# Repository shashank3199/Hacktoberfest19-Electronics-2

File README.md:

# Electronics-2

## Introduction
This repository contains the board design for Manual Bot Controller Shield for Arduino Mega 2560.

## Layout

### Board File -

### Schematic File -

## Files in the Repository
The files in the repository are :

#### ManualBot_Shield.brd
This is the Board file and contains the Blueprint of the Shield Layout (Prototype).

#### ManualBot_Shield.sch
This is the Schematic file and contains the actual circuitary behind the Shield.

#### README.md
The Description file containing details about the repository. The file that you looking at right now.

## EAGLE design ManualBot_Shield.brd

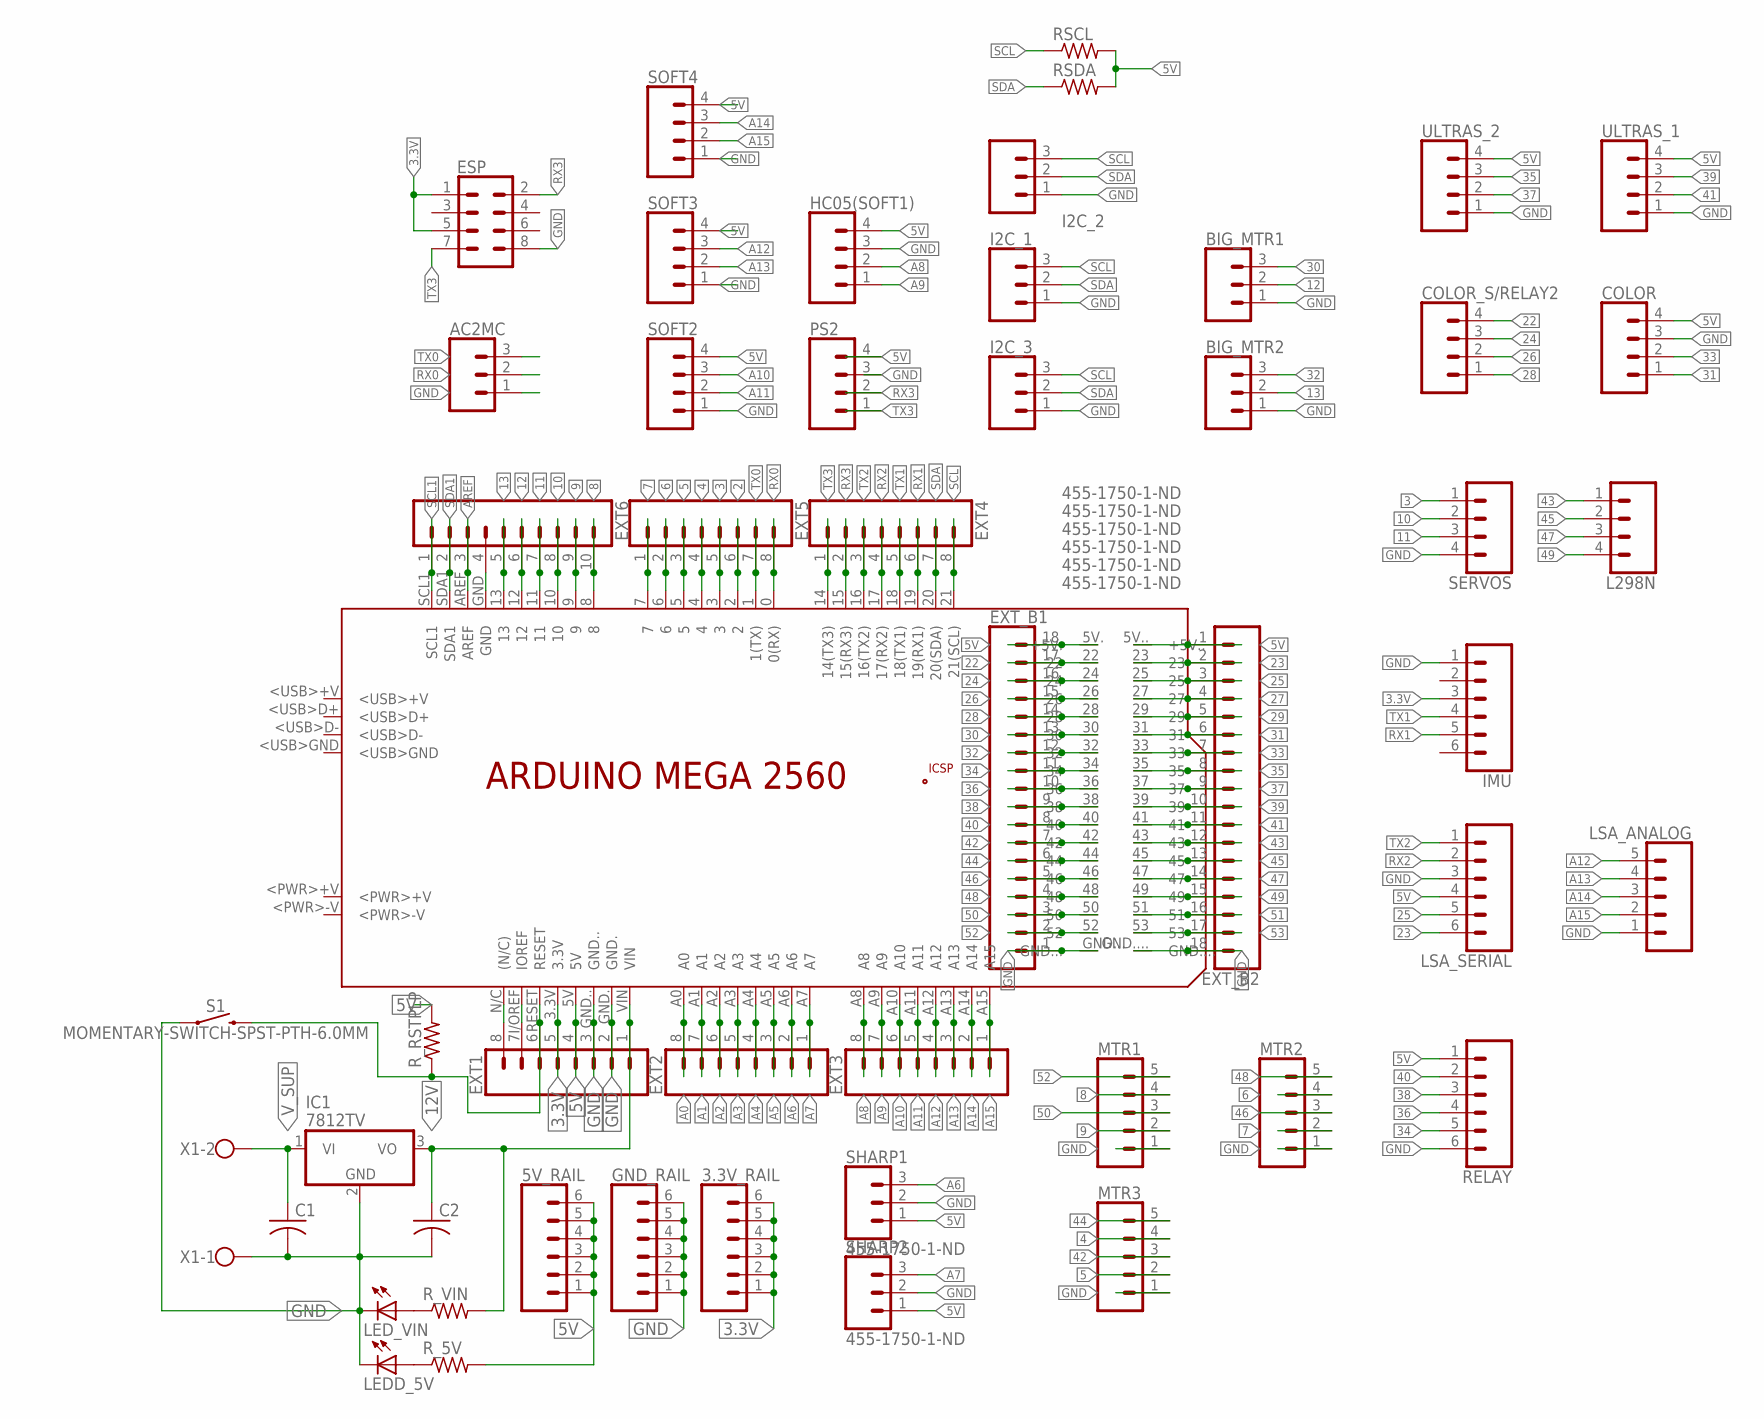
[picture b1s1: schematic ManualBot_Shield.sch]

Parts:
3.3V_RAIL, 5V_RAIL: CONN_06SILK_FEMALE_PTH; 1X06
AC2MC: 455-1750-1-ND; 1X03
BIG_MTR1, BIG_MTR2: 455-1750-1-ND; 1X03
C1, C2: C-US025-024X044; C025-024X044
COLOR: CONN_04; 1X04
COLOR_S/RELAY2: CONN_04; 1X04
ESP: CONN_04X2; 2X4
EXT1, EXT2, EXT3, EXT4, EXT5: CONN_08"; 1X08
EXT6: CONN_10"; 1X10
EXT_B1, EXT_B2: CONN_18; 1X18_NO_SILK
GND_RAIL: CONN_06SILK_FEMALE_PTH; 1X06
HC05(SOFT1): CONN_04; 1X04
I2C_1, I2C_2, I2C_3: 455-1750-1-ND; 1X03
IC1: 7812TV; TO220V
IMU: CONN_06SILK_FEMALE_PTH; 1X06
L298N: CONN_04; 1X04
LEDD_5V: LED5MM
LED_VIN: LED5MM
LSA_ANALOG: CONN_05; 1X05
LSA_SERIAL: CONN_06SILK_FEMALE_PTH; 1X06
MTR1, MTR2, MTR3: CONN_05; 1X05
PCB1: ARDUINO_MEGA2560
PS2: CONN_04; 1X04
RELAY: CONN_06SILK_FEMALE_PTH; 1X06
RSCL: R-US_0204/7; 0204/7
RSDA: R-US_0204/7; 0204/7
R_5V: R-US_0204/7; 0204/7
R_RSTPLP: R-US_0204/7; 0204/7
R_VIN: R-US_0204/7; 0204/7
S1: MOMENTARY-SWITCH-SPST-PTH-6.0MM; TACTILE_SWITCH_PTH_6.0MM
SERVOS: CONN_04; 1X04
SHARP1, SHARP2: 455-1750-1-ND; 1X03
SOFT2, SOFT3, SOFT4: CONN_04; 1X04
ULTRAS_1, ULTRAS_2: CONN_04; 1X04
X1: W237-102

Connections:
2: EXT5.6, PCB1.2
3: EXT5.5, PCB1.3, SERVOS.1
3.3V: 3.3V_RAIL.1, 3.3V_RAIL.2, 3.3V_RAIL.3, 3.3V_RAIL.4, 3.3V_RAIL.5, 3.3V_RAIL.6, ESP.1, ESP.5, EXT1.5, IMU.3, PCB1.3.3V
4: EXT5.4, MTR3.4, PCB1.4
5: EXT5.3, MTR3.2, PCB1.5
5V: 5V_RAIL.1, 5V_RAIL.2, 5V_RAIL.3, 5V_RAIL.4, 5V_RAIL.5, 5V_RAIL.6, COLOR.4, EXT1.4, EXT_B1.18, EXT_B2.1, HC05(SOFT1).4, LSA_SERIAL.4, PCB1.5V, PCB1.5V. (+5V.), PCB1.5V.. (+5V..), PS2.4, RELAY.1, RSCL.2, RSDA.2, R_5V.2, R_RSTPLP.2, SHARP1.1, SHARP2.1, SOFT2.4, SOFT3.4, SOFT4.4, ULTRAS_1.4, ULTRAS_2.4
6: EXT5.2, MTR2.4, PCB1.6
7: EXT5.1, MTR2.2, PCB1.7
8: EXT6.10, MTR1.4, PCB1.8
9: EXT6.9, MTR1.2, PCB1.9
10: EXT6.8, PCB1.10, SERVOS.2
11: EXT6.7, PCB1.11, SERVOS.3
12: BIG_MTR1.2, EXT6.6, PCB1.12
12V: C2.1, EXT1.1, IC1.3 (VO), PCB1.VIN, R_VIN.2
13: BIG_MTR2.2, EXT6.5, PCB1.13
22: COLOR_S/RELAY2.4, EXT_B1.17, PCB1.22
23: EXT_B2.2, LSA_SERIAL.6, PCB1.23
24: COLOR_S/RELAY2.3, EXT_B1.16, PCB1.24
25: EXT_B2.3, LSA_SERIAL.5, PCB1.25
26: COLOR_S/RELAY2.2, EXT_B1.15, PCB1.26
27: EXT_B2.4, PCB1.27
28: COLOR_S/RELAY2.1, EXT_B1.14, PCB1.28
29: EXT_B2.5, PCB1.29
30: BIG_MTR1.3, EXT_B1.13, PCB1.30
31: COLOR.1, EXT_B2.6, PCB1.31
32: BIG_MTR2.3, EXT_B1.12, PCB1.32
33: COLOR.2, EXT_B2.7, PCB1.33
34: EXT_B1.11, PCB1.34, RELAY.5
35: EXT_B2.8, PCB1.35, ULTRAS_2.3
36: EXT_B1.10, PCB1.36, RELAY.4
37: EXT_B2.9, PCB1.37, ULTRAS_2.2
38: EXT_B1.9, PCB1.38, RELAY.3
39: EXT_B2.10, PCB1.39, ULTRAS_1.3
40: EXT_B1.8, PCB1.40, RELAY.2
41: EXT_B2.11, PCB1.41, ULTRAS_1.2
42: EXT_B1.7, MTR3.3, PCB1.42
43: EXT_B2.12, L298N.1, PCB1.43
44: EXT_B1.6, MTR3.5, PCB1.44
45: EXT_B2.13, L298N.2, PCB1.45
46: EXT_B1.5, MTR2.3, PCB1.46
47: EXT_B2.14, L298N.3, PCB1.47
48: EXT_B1.4, MTR2.5, PCB1.48
49: EXT_B2.15, L298N.4, PCB1.49
50: EXT_B1.3, MTR1.3, PCB1.50
51: EXT_B2.16, PCB1.51
52: EXT_B1.2, MTR1.5, PCB1.52
53: EXT_B2.17, PCB1.53
A0: EXT2.8, PCB1.A0
A1: EXT2.7, PCB1.A1
A2: EXT2.6, PCB1.A2
A3: EXT2.5, PCB1.A3
A4: EXT2.4, PCB1.A4
A5: EXT2.3, PCB1.A5
A6: EXT2.2, PCB1.A6, SHARP1.3
A7: EXT2.1, PCB1.A7, SHARP2.3
A8: EXT3.8, HC05(SOFT1).2, PCB1.A8
A9: EXT3.7, HC05(SOFT1).1, PCB1.A9
A10: EXT3.6, PCB1.A10, SOFT2.3
A11: EXT3.5, PCB1.A11, SOFT2.2
A12: EXT3.4, LSA_ANALOG.5, PCB1.A12, SOFT3.3
A13: EXT3.3, LSA_ANALOG.4, PCB1.A13, SOFT3.2
A14: EXT3.2, LSA_ANALOG.3, PCB1.A14, SOFT4.3
A15: EXT3.1, LSA_ANALOG.2, PCB1.A15, SOFT4.2
AREF: EXT6.3, PCB1.AREF
GND: AC2MC.1, BIG_MTR1.1, BIG_MTR2.1, C1.2, C2.2, COLOR.3, ESP.8, EXT1.2, EXT1.3, EXT6.4, EXT_B1.1, EXT_B2.18, GND_RAIL.1, GND_RAIL.2, GND_RAIL.3, GND_RAIL.4, GND_RAIL.5, GND_RAIL.6, HC05(SOFT1).3, I2C_1.1, I2C_2.1, I2C_3.1, IC1.2 (GND), IMU.1, LEDD_5V.K (C), LED_VIN.K (C), LSA_ANALOG.1, LSA_SERIAL.3, MTR1.1, MTR2.1, MTR3.1, PCB1.GND, PCB1.GND., PCB1.GND.., PCB1.GND..., PCB1.GND...., PS2.3, RELAY.6, S1.1, SERVOS.4, SHARP1.2, SHARP2.2, SOFT2.1, SOFT3.1, SOFT4.1, ULTRAS_1.1, ULTRAS_2.1, X1.1
unnamed: LED_VIN.A, R_VIN.1
unnamed: LEDD_5V.A, R_5V.1
unnamed: EXT1.6, PCB1.RESET, R_RSTPLP.1, S1.3 (2)
unnamed: EXT1.7, PCB1.I/OREF (IOREF)
unnamed: EXT1.8, PCB1.N/C ((N/C))
RX0: AC2MC.2, EXT5.8, PCB1.0 (0(RX))
RX1: EXT4.6, IMU.5, PCB1.19 (19(RX1))
RX2: EXT4.4, LSA_SERIAL.2, PCB1.17 (17(RX2))
RX3: ESP.2, EXT4.2, PCB1.15 (15(RX3)), PS2.2
SCL: EXT4.8, I2C_1.3, I2C_2.3, I2C_3.3, PCB1.21 (21(SCL)), RSCL.1
SCL1: EXT6.1, PCB1.SCL1
SDA: EXT4.7, I2C_1.2, I2C_2.2, I2C_3.2, PCB1.20 (20(SDA)), RSDA.1
SDA1: EXT6.2, PCB1.SDA1
TX0: AC2MC.3, EXT5.7, PCB1.1 (1(TX))
TX1: EXT4.5, IMU.4, PCB1.18 (18(TX1))
TX2: EXT4.3, LSA_SERIAL.1, PCB1.16 (16(TX2))
TX3: ESP.7, EXT4.1, PCB1.14 (14(TX3)), PS2.1
V_SUP: C1.1, IC1.1 (VI), X1.2

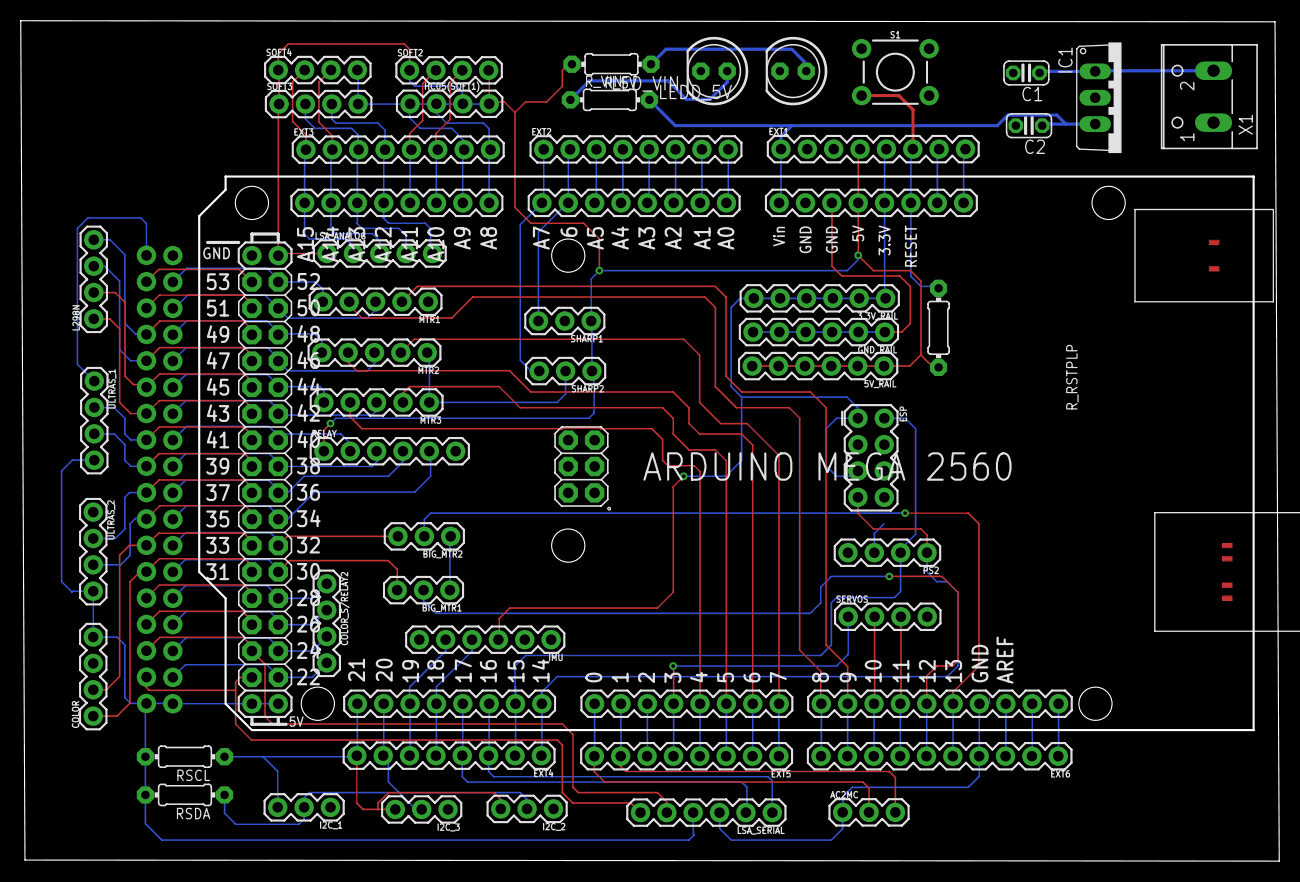
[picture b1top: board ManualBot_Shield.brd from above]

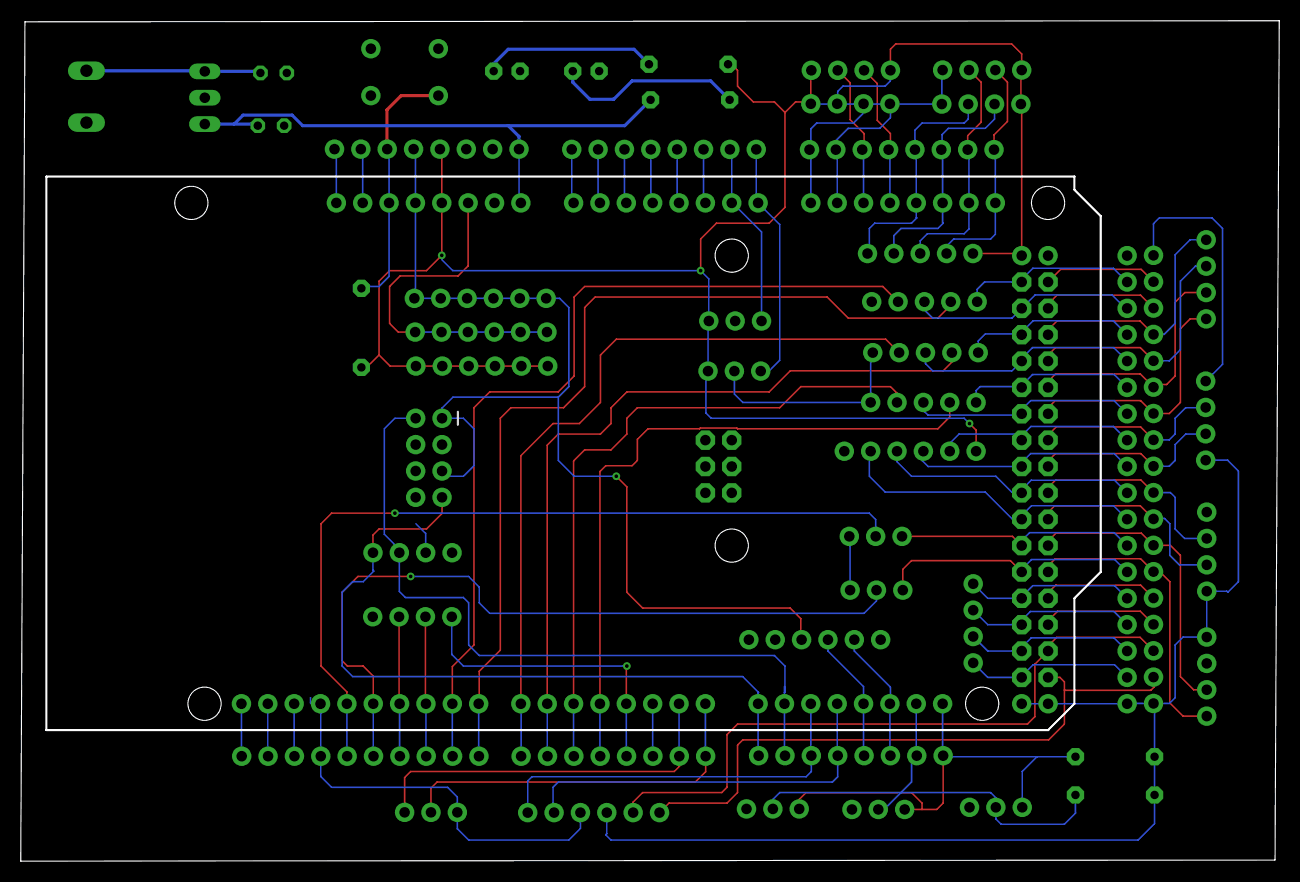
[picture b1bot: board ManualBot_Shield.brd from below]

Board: 2 copper layers, 121.1 x 80.8 mm, 51 parts (2 on the bottom side), 83 nets.

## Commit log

2019-10-02 comet2
2019-10-20 Added Documentation and Appropriate Naming
2019-10-20 Fixed Documentation

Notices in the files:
parts and their libraries:
SparkFun-Connectors: Licensing: Creative Commons ShareAlike 4.0 International - https://creativecommons.org/licenses/by-sa/4.0
